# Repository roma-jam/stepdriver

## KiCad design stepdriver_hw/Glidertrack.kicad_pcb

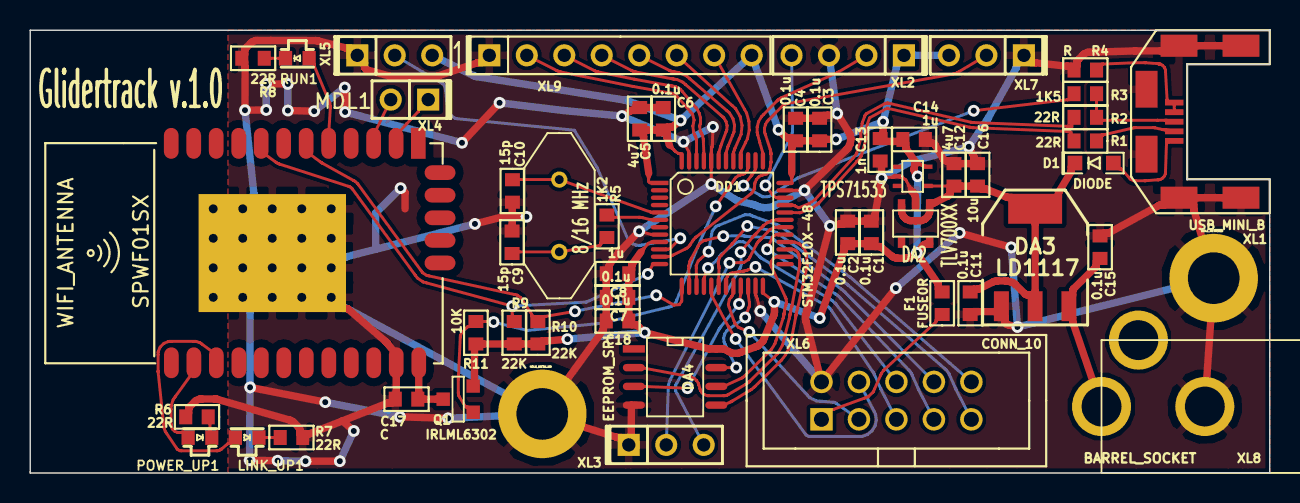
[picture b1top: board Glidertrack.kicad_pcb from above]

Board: 2 copper layers, 84.0 x 30.0 mm, 53 parts (0 on the bottom side), 52 nets.

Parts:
C1, C2, C3, C4, C6, C7, C11, C15, C18: 0.1u; CAP_0603
C5, C12: 4u7; CAP_0603
C8, C14: 1u; CAP_0603
C9, C10: 15p; CAP_0603
C13: 1n; CAP_0603
C16: 10u; CAP_0603
C17: C; CAP_0603
D1: DIODE; DIODE_SOD323
DA1: TPS71533; SOT323
DA2: TLV700XX; SOT23-5
DA3: LD1117; SOT223
DA4: EEPROM_SPI; SO8E
DD1: STM32F10X-48; LQFP48
F1: FUSE0R; RES_0603
HOLE1, HOLE2: HOLE_METALLED; Hole3_5_out6mm
LINK_UP1: LED; LED_ANGLE
MDL1: SPWF01SX; SPWF01SX_FOOT
POWER_UP1: LED; LED_ANGLE
Q1: IRLML6302; SOT23
R1, R2, R6, R7, R8: 22R; RES_0603
R3: 1K5; RES_0603
R4: R; RES_0603
R5: 1K2; RES_0603
R9, R10: 22K; RES_0603
R11: 10K; RES_0603
RUN1: LED; LED_ANGLE
XL1: USB_MINI_B; USBmicro_MOLEX_WM17142
XL2: ST_SWD; CONN_PLS-4
XL3, XL5, XL7: CONN_3; CONN_PLS-3
XL4: CONN_2; CONN_PLS-2
XL6: CONN_10; CONN_IDC_2X5
XL8: BARREL_SOCKET; CONN_BARREL
XL9: CONN_8; CONN_PLS-8
XTAL1: 8/16 MHz; CRYSTAL_HC49

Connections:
+3.3V: C1.1, C2.1, C3.1, C4.1, C5.1, C6.1, C7.1, C8.1, C13.1, C14.1, C18.1, DA1.5, DA2.5, DA4.8, DD1.1, DD1.9, DD1.24, DD1.36, DD1.48, F1.2, Q1.2, R9.1, R10.1, R11.1, XL2.1, XL5.3, XL7.3, XL9.8
+5V: C11.1, C12.1, C16.1, D1.C, DA1.4, DA2.1, DA2.3, DA3.2, DA3.PAD
+12V: C15.1, DA3.3, XL8.PWR
/DEBUG_RX: DD1.31, XL3.3
/DEBUG_TX: DD1.30, XL3.2
/EE_HOLD: DA4.7, DD1.22
/EE_MISO: DA4.2, DD1.27
/EE_MOSI: DA4.5, DD1.28
/EE_SCK: DA4.6, DD1.26
/EE_WRITE: DA4.3, DD1.21
/ENDSTOP1: DD1.10, XL5.2
/ENDSTOP2: DD1.11, XL7.2
/GPIOB4: DD1.40, XL9.7
/GPIOB5: DD1.41, XL9.6
/GPIOB6: DD1.42, XL9.5
/GPIOB7: DD1.43, XL9.4
/GPIOB8: DD1.45, XL9.3
/GPIOB9: DD1.46, XL9.2
/MOTOR_BUSY: DD1.19, XL6.5
/MOTOR_FLAG: DD1.20, XL6.3
/MOTOR_SPI_CS: DD1.14, XL6.8
/MOTOR_SPI_MISO: DD1.16, XL6.6
/MOTOR_SPI_MOSI: DD1.17, XL6.4
/MOTOR_SPI_SCK: DD1.15, XL6.10
/MOTOR_STBY: DD1.18, XL6.9
/MOTOR_STCK: DD1.29, XL6.7
/PWR: C17.1, MDL1.24, Q1.3
/SWCLK: DD1.37, XL2.2
/SWDIO: DD1.34, XL2.4
/USB_CABLE: DD1.38, R3.1
/USB_DM: DD1.32, R1.2
/USB_DP: DD1.33, R2.1
/WIFI_BOOT: MDL1.2, XL4.1
/WIFI_PWR: DD1.39, Q1.1, R11.2
/WIFI_RESET: MDL1.3, XL4.2
/WIFI_RX: DD1.13, MDL1.6, R10.2
/WIFI_TX: DD1.12, MDL1.8, R9.2
GND: C1.2, C2.2, C3.2, C4.2, C5.2, C6.2, C7.2, C8.2, C9.2, C10.2, C11.2, C12.2, C13.2, C14.2, C15.2, C16.2, C17.2, C18.2, DA1.2, DA2.2, DA3.1, DA4.4, DD1.8, DD1.23, DD1.35, DD1.44, DD1.47, HOLE1.Hle, HOLE2.Hle, MDL1.23, MDL1.PAD, R4.1, R6.2, R7.2, R8.2, XL1.SHLD, XL2.3, XL3.1, XL5.1, XL6.2, XL7.1, XL8.GND, XL9.1
unnamed: F1.1, XL6.1
unnamed: DD1.6, R5.1
unnamed: MDL1.14, POWER_UP1.A
unnamed: LINK_UP1.A, MDL1.15
unnamed: MDL1.5, RUN1.A
unnamed: POWER_UP1.C, R6.1
unnamed: LINK_UP1.C, R7.1
unnamed: R8.1, RUN1.C
unnamed: R4.2, XL1.4, XL1.5
unnamed: R1.1, XL1.2
unnamed: R2.2, R3.2, XL1.3
unnamed: C9.1, R5.2, XTAL1.1
unnamed: C10.1, DD1.5, XTAL1.2
unnamed: D1.A, XL1.1

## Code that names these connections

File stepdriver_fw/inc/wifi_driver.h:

/*
 * wifi_driver.h
 *
 *  Created on: 20 íîÿá. 2014 ã.
 *      Author: r.leonov
 */

#ifndef WIFI_DRIVER_H_
#define WIFI_DRIVER_H_

#include "kl_lib_f100.h"
#include "round_buf.h"

/* INFO
 * <cr><lf>+WIND:<number>:<descriptive string><cr><lf> asynchronius command
 *
 * AT<cmd><cr>
 * <zero or more response lines><cr><lf>
 * <responsecode><cr><lf>
 */


#define WIFI_UART           USART2
#define WIFI_Clock_EN()     rccEnableUSART2(FALSE);
#define WIFI_TX_DMA         STM32_DMA1_STREAM7
#define WIFI_IRQ_Handler    USART2_IRQHandler
#define WIFI_IRQ            USART2_IRQn

#define WIFI_DMA_MODE       STM32_DMA_CR_PL(0b10)   |  /* Priority is high */  \
                            STM32_DMA_CR_MSIZE_BYTE | \
                            STM32_DMA_CR_PSIZE_BYTE | \
                            STM32_DMA_CR_MINC       |  /* Memory pointer increase*/ \
                            STM32_DMA_CR_DIR_M2P    |  /* Direction is memory to peripheral*/ \
                            STM32_DMA_CR_TCIE           // Enable Transmission Complete IRQ

#define WIFI_GPIO           GPIOA
#define WIFI_TX_PIN         2
#define WIFI_RX_PIN         3
#define WIFI_BAUDRATE       115200

#define WIFI_CMD_BUF_SZ     128     // Maximum Command Length is 127 character (um p. 5)
#define WIFI_RX_BYTE        WIFI_UART->DR

#define WIFI_PWR_GPIO       GPIOB
#define WIFI_PWR_PIN        3

class wifi_driver_t {
private:
    uint8_t HostBuf[WIFI_CMD_BUF_SZ];
    uint8_t *pRead;
    Thread *PWaitThd;
    bool WiFiDmaIsIdle;
    uint32_t ITransmitSize, SlotsFilled;
    void IHandleByte();
    void IWaitTxEnd() {
        chSysLock();
        PWaitThd = chThdSelf();
        chSchGoSleepS(THD_STATE_SUSPENDED);
        chSysUnlock();
    }
    void ITxEnd() {
        if(PWaitThd != NULL) {
            chSysLockFromIsr();
            chSchReadyI(PWaitThd);
            chSysUnlockFromIsr();
        }
    }
public:
    round_buf_t RplBuf;
    void Init();
    void CmdSend(uint8_t *PBuf, uint32_t Length);
    void CmdSendDma();
    void PowerOn()  { PinClear(WIFI_PWR_GPIO, WIFI_PWR_PIN); }
    void PowerOff() { PinSet  (WIFI_PWR_GPIO, WIFI_PWR_PIN); }
    void IRQ_RxHandler();
    void IRQ_TxHandler();
};

extern wifi_driver_t WiFi;

#endif /* WIFI_DRIVER_H_ */

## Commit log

2014-02-19 First working copy of Sincahonda project.
2014-02-19 Stage commit to start new branch.
2014-02-19 + Move usb relative to usb folder.
2014-02-19 + Application and cleanup code.
2014-02-19 + Switched logic from tiny_sprintf to kl_sprintf.
2014-02-19 + Service msg to update numbers of motor.
2014-02-19 + Srv msg correct parse.
2014-02-19 + Cmd parse ended. Sometimes occured bug in kl_sprint!! WARNING.
2014-02-19 + Fixed CmdID in CmdExecute; Increase buffer size in UART dbg.
2014-02-19 + Worked with new cmd handler.
2014-02-19 + Small fixes.
2014-02-21 + Fixed motor count size and cmd with wrong motor number.
2014-04-09 + StepClk mode done.
2014-05-07 Step clock cmd.
2014-05-07 Start vcp project.
2014-05-07 Pill_mgr implemented.
2014-05-07 Ping cmd working well.
2014-05-08 Try to change logic to text-protocol.
2014-10-02 REMOVE: pillmgr.* files; ADD: motor driver files.
2014-10-02 Start to write driver logic
2014-10-02 Commands proceed
2014-10-02 Commands done.
2014-10-02 FIX: Different size of register need different count of read operation. Correct now.
2014-10-07 FIX: reception command by usb bigger then 1 byte.
2014-10-07 ADD: excel file with costs.
2014-10-08 Move to new command protocol. ADD: Timelapse setup.
2014-10-09 Timelapse done
2014-11-20 Small fixes: output maxstepsize to VCP.
2014-11-20 ADD: WiFi driver started.
2014-11-20 Proceed AT parse.
2014-11-21 ADD: round buf files. Up chibiOS debug assert.
2014-11-26 ADD: html files.
2014-11-26 Move to directory stepdriver_fw.
2014-11-26 Glidertrack_hw added.
2014-11-26 stage
2014-11-27 ADD: Http_Server, getting AT answer "+WIND" OK! Start to parse msg.
2014-11-27 Proceed parsing AT command.
2014-11-27 Dma send done.
2014-11-27 Start to parsing http request.
2014-11-27 Action event added.
2014-11-27 previous
2014-11-27 Try to HTTP post correctly.
2014-12-05 HW: start to trace pcb.
2014-12-10 HW: component placed.
2014-12-11 HW: added MOSFET transistor on power WiFi module.
2014-12-30 HW: PCB design proceed.
2014-12-30 HW: PCB design complete.
2015-01-14 HW: add gerber files.
2015-03-14 Migrating wiki contents from Google Code
2015-03-14 Add power pin, change crystal value to 16 Mhz.
2015-03-14 Switch to STM descriptors.
2015-03-14 Working, but not correct. Check the length of the page and send all the buffer in one time (maybe).
2015-08-08 Add: EEPROM files and beeper files. Small changes.
2015-08-08 Add endstops files and init done.
2015-08-08 Hit/Release state added.
2015-08-08 Hit/Release functions done.
2016-04-02 + Beeper + Endstops
2016-04-02 Add short index html page
2016-04-02 Update ignore list
2016-04-07 Fix EE_CS
2016-06-05 Follow up
2016-06-05 + Add config + Fix EEPROM write\read
2016-06-05 + WiFi Commands
2016-06-05 stack overflow @Motor
2016-06-05 + Endstop event in app
2016-06-08 Should to rewrite all low level logic of motor driver
2016-06-10 Start to rewrite motor logic
2016-06-10 Low level SPI ready
2016-06-11 Spi doesnt work in some reaseon
2016-06-11 Proceed to find problem
2016-06-11 Disable low level debug
2016-06-11 Fix SPI problem :)
2016-06-11 + EEPROM config driver
2016-06-11 EEPROM Config data saving ok Calibration done
2016-06-11 Increase calibrate speed
2016-06-13 try to do wifi on AP
2018-11-25 + Update index.htm + Update clocking
